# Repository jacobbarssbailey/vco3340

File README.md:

# VCO3340
This project provides tested plans for a 6HP Eurorack-format CEM3340 [CoolAudio 3340] VCO synthesizer module.

### Inputs
- V/OCT: Exponential (1V per octave) pitch input
- Lin FM: Linear frequency modulation
- Sync: Hard sync oscillator to external signal; requires audio-rate signal at approx. ±5V.
- Width: Set duty cycle of pulse output from 0-100% with ±2.5V signal; normalled to 0V, i.e. square wave output

### Outputs
All oscillator outputs (Sine, Triangle, Sawtooth, and Pulse) range from ±5V. The pulse input width is controlled by the Width input, and by default is a 50% duty cycle, i.e. Square wave.

## BOM 

Qty | Value            | Device                  | Package             | Parts                                                |
--- | ---------------- | ----------------------- | ------------------- | ---------------------------------------------------- |
2   | 10KΩ             | Pot (Alpha 9mm)         | 6mm                 | COURSE, FINE                                         |
8   | 3.5mm Jacks      |                         | Thonkiconn          | LINFM, PULSE, SAW, SIN, SYNC, TRI, V/OCT, WIDTH      |
4   | M06              | 2.54mm header           | Pin                 | CTRL, KNOB, OUT, POWER                               |
4   | M06              | 2.54mm header           | Socket              | CTRL, KNOB, OUT, POWER                               |
1   | M08X2            | 2.54mm header           | Pin                 | EXPANSION                                            |
3   |                  | 2.54mm                  | Jumper              |                                                      |
1   | M05x2            | 2.54mm header           | Shrouded            | POWER                                                |
2   | 100Ω             | Resistor                | 0805                | R1, R22                                              |
1   | 390Ω             | Resistor                | 0805                | R36                                                  |
2   | 470Ω             | Resistor                | 0805                | R9, R19                                              |
1   | 1KΩ              | Resistor                | 0805                | R32                                                  |
2   | 2.2KΩ            | Resistor                | 0805                | R34, R40                                             |
2   | 3.6KΩ            | Resistor                | 0805                | R23, R25                                             |
1   | 5.6KΩ            | Resistor                | 0805                | R2, R21                                              |
8   | 10KΩ             | Resistor                | 0805                | R5, R10, R27, R35, R38, R39, R41, R42                |
1   | 24KΩ             | Resistor                | 0805                | R20                                                  |
1   | 47KΩ             | Resistor                | 0805                | R3                                                   |
2   | 80KΩ             | Resistor                | 0805                | R28, R29                                             |
5   | 100KΩ            | Resistor                | 0805                | R4, R15, R16, R24, R30                               |
4   | 200KΩ            | Resistor                | 0805                | R14, R18, R26, R31                                   |
1   | 150KΩ            | Resistor                | 0805                | R6                                                   |
3   | 1MΩ              | Resistor                | 0805                | R7, R11, R13                                         |
1   | 1.5MΩ            | Resistor                | 0805                | R8                                                   |
2   | 1.0nF            | Capacitor               | 0805                | C1, C2                                               |
1   | 1.25nF           | Capacitor (CG0)         | 0805                | C6                                                   |
2   | 10nF             | Capacitor               | 0805                | C4, C5                                               |
11  | 100nF            | Capacitor               | 0805                | C3, C10, C11, C12, C13, C14, C15, C18, C19, C21, C22 |
2   | 1µF              | Capacitor               | 0805                | C8, C9                                               |
4   | 47µF             | Capacitor (Pol)         | PANASONIC_C         | C16, C17, C20, C23                                   |
1   | 10KΩ             | Trimpot                 | 2.54mm Multiturn    | SCALE                                                |
1   | 20KΩ             | Trimpot                 | 2.54mm Multiturn    | HIGHFREQ                                             |
1   | 50KΩ             | Trimpot                 | 2.54mm Multiturn    | SYMMETRY                                             |
1   | 100KΩ            | Trimpot                 | 2.54mm Multiturn    | DRIVE                                                |
2   |                  | DIODE                   | SOD-123             | D4, D5                                               |
3   |                  | DIODE                   | SOD-323             | D1, D2, D3                                           |
2   | 3904             | Transistor (NPN)        | SOT23               | Q1, Q2                                               |
1   |                  | LM79L05A                | SOT89               | U1                                                   |
1   |                  | MC78L05A                | SOT89               | U2                                                   |
1   | TL071            | OPAMP-SINGLE            | SO08                | IC1                                                  |
1   |                  | V3340/CEM3340           | SO16                | IC2                                                  |
1   |                  | LM397                   | SOT23-5             | IC3                                                  |
2   | TL072            | OPAMP-DUAL              | SO08                | IC4, IC5                                             |

## Notes on assembly:
1. The rear expansion header is not optional; the V/Oct, Pulse Width, and Soft Sync inputs *must* be connected to ground for proper operation
1. Non-shrouded headers may be used for the Power connector, but this makes it easier to invert the cable polarity, with potentially unpleasant results.

## First time setup
The four trim potentiometers must be set up before use. The following procedure is recommended:
1. Confirm that the V/Oct, Pulse Width, and Soft Sync inputs on the expansion header are connected to the neighboring ground pin (with jumpers)
1. Turn HIGHFREQ all the way down. The middle pin should be shorted to ground.
1. Adjust SCALE until V/Oct input tracks at 1V per octave from 40-60Hz to ≅2Khz. This step is the most difficult, but its critical for tuning. If available, compare against a reference VCO with good tracking. Alternative methods include measuring the pulse output with a frequency counter, or measuring with an external tuner.
1. Adjust HIGHFREQ up until higher frequencies track equally well.
1. Measure the SINE output. Adjust DRIVE and SYMMETRY until the output sounds like a Sine Wave. Using an Oscilloscope may make this easiest, but its not critical and your ears are an equally good reference.

## Expansion header

While the module is an excellent standalone module, the rear expansion header may be used to add additional controls or further manipulate outputs.

It can provide power rails to a sister module, but the ±5V rails should be limited to <50mA.

The external V/Oct pin duplicates the front-panel input. The Width input sets the default pulse width. The Soft Sync input is ready to use as is, and expects ±5V audio rate signals as input.

All output waveforms are provided for additional waveshaping.

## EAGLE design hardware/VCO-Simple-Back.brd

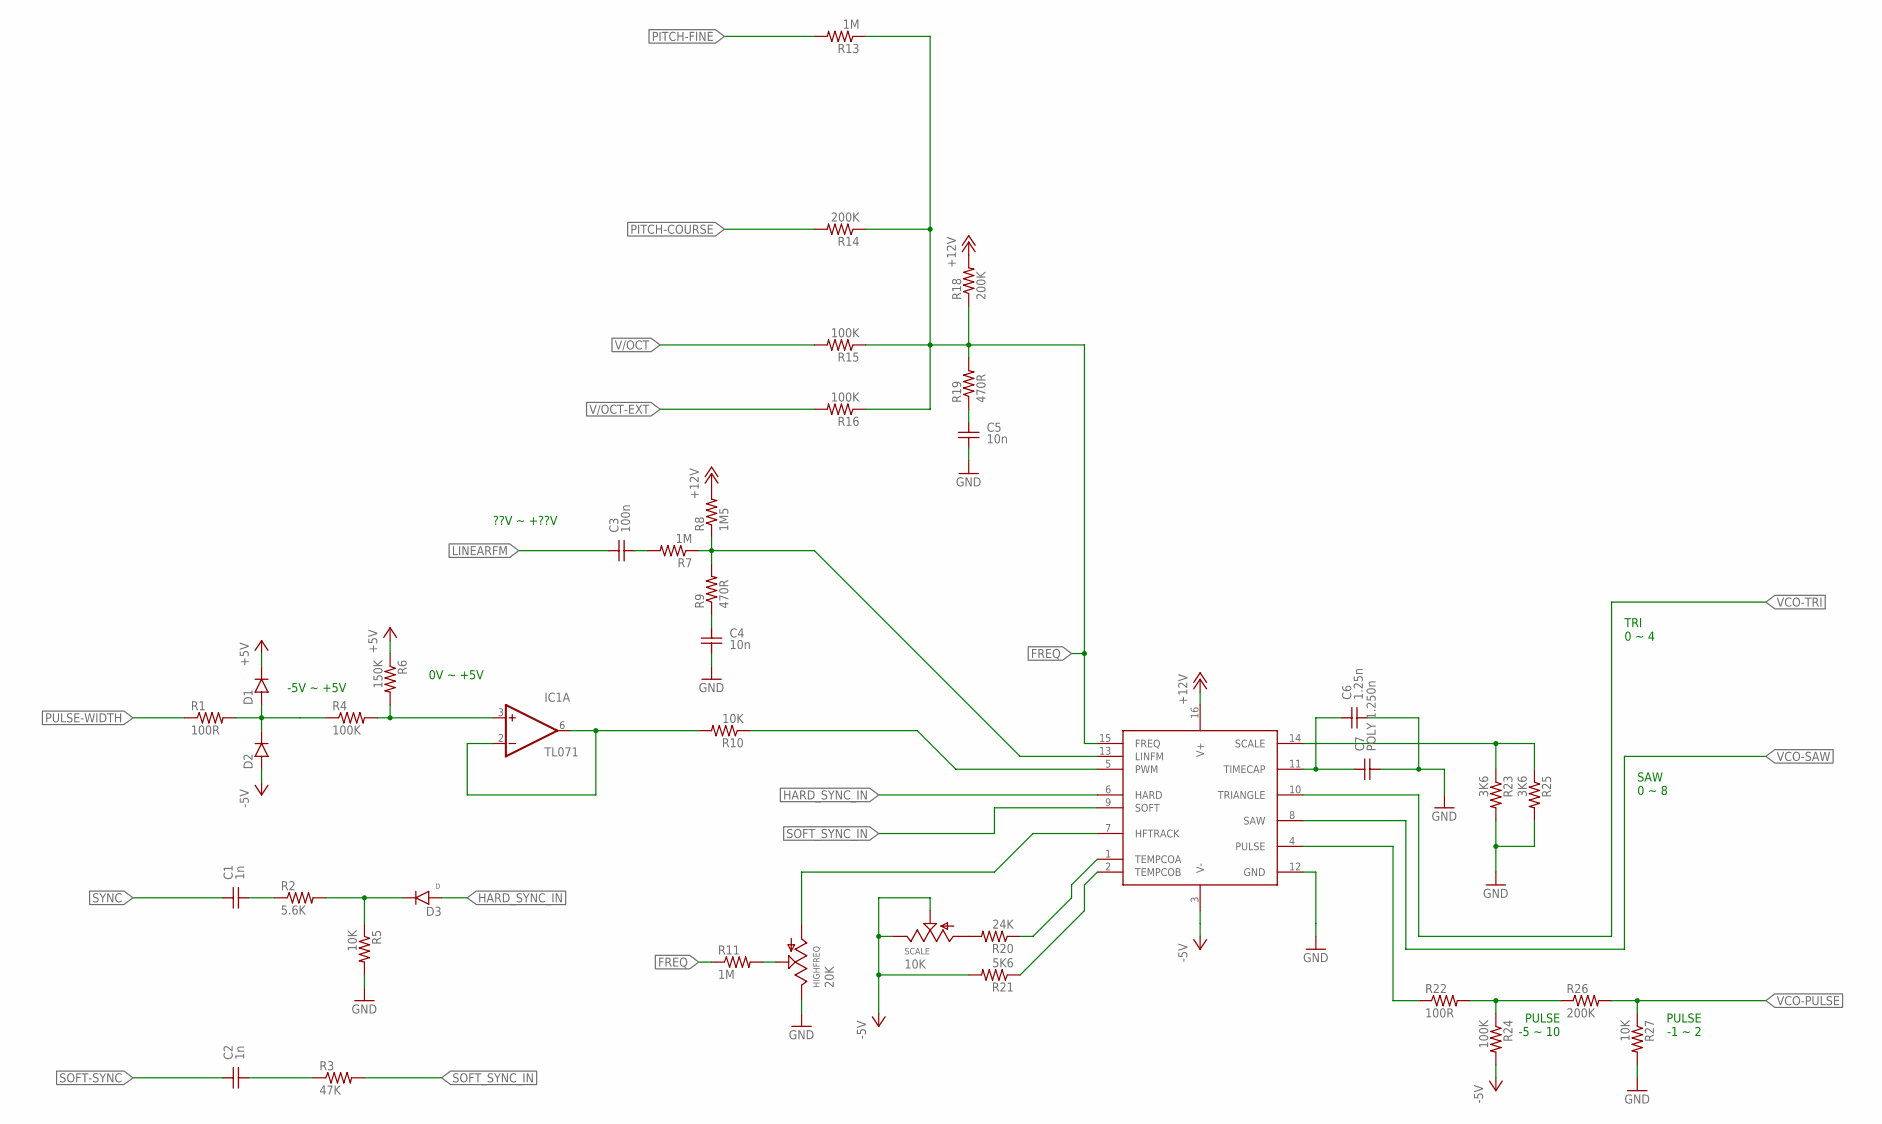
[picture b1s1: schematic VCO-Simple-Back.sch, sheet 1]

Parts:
C1, C2: 1n; C-0805
C3: 100n; C-0805
C4, C5: 10n; C-0805
C6: 1.25n; C-0805
C7: POLY 1.250n; CAP-5MM
D1, D2: DIODESOD-323; SOD-323
D3: D; SOD-323
HIGHFREQ: 20K; POT-TRIM-MULTI-V
IC1: TL071; SO08
IC2: V3340SO16; SO16
R1, R22: 100R; R-0805-MILL
R2: 5.6K; R-0805-MILL
R3: 47K; R-0805-MILL
R4, R15, R16, R24: 100K; R-0805-MILL
R5, R10, R27: 10K; R-0805-MILL
R6: 150K; R-0805-MILL
R7, R11, R13: 1M; R-0805-MILL
R8: 1M5; R-0805-MILL
R9, R19: 470R; R-0805-MILL
R14, R18, R26: 200K; R-0805-MILL
R20: 24K; R-0805-MILL
R21: 5K6; R-0805-MILL
R23, R25: 3K6; R-0805-MILL
SCALE: 10K; POT-TRIM-MULTI-V

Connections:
+5V: D1.K (C), R6.P$1 (1); also elsewhere on the board
+12V: IC2.16 (V+), R8.P$2 (2), R18.P$2 (2); also elsewhere on the board
-5V: D2.A, IC2.3 (V-), R21.P$2 (2), R24.P$2 (2), SCALE.B (E), SCALE.W (S); also elsewhere on the board
FREQ: IC2.15 (FREQ), R11.P$1 (1), R13.P$1 (1), R14.P$1 (1), R15.P$1 (1), R16.P$1 (1), R18.P$1 (1), R19.P$2 (2)
GND: C4.2, C5.2, C6.2, C7.2, HIGHFREQ.B (E), IC2.12 (GND), R5.P$2 (2), R23.P$2 (2), R25.P$2 (2), R27.P$2 (2); also elsewhere on the board
HARD_SYNC_IN: D3.A, IC2.6 (HARD)
LINEARFM: C3.1; also elsewhere on the board
unnamed: IC2.5 (PWM), R10.P$1 (1)
unnamed: C6.1, C7.1, IC2.11 (TIMECAP)
unnamed: HIGHFREQ.W (S), R11.P$2 (2)
unnamed: R20.P$2 (2), SCALE.A
unnamed: IC2.2 (TEMPCOB), R21.P$1 (1)
unnamed: D3.K (C), R2.P$2 (2), R5.P$1 (1)
unnamed: IC2.14 (SCALE), R23.P$1 (1), R25.P$1 (1)
unnamed: C5.1, R19.P$1 (1)
unnamed: C3.2, R7.P$2 (2)
unnamed: IC2.13 (LINFM), R7.P$1 (1), R8.P$1 (1), R9.P$2 (2)
unnamed: C4.1, R9.P$1 (1)
unnamed: HIGHFREQ.A, IC2.7 (HFTRACK)
unnamed: IC2.1 (TEMPCOA), R20.P$1 (1)
unnamed: D1.A, D2.K (C), R1.P$2 (2), R4.P$1 (1)
unnamed: R22.P$2 (2), R24.P$1 (1), R26.P$1 (1)
unnamed: C1.2, R2.P$1 (1)
unnamed: C2.2, R3.P$1 (1)
unnamed: IC1.3 (+IN), R4.P$2 (2), R6.P$2 (2)
PITCH-COURSE: R14.P$2 (2); also elsewhere on the board
PITCH-FINE: R13.P$2 (2); also elsewhere on the board
PULSE: IC2.4 (PULSE), R22.P$1 (1)
PULSE-WIDTH: R1.P$1 (1); also elsewhere on the board
PWMIN: IC1.2 (-IN), IC1.6 (OUT), R10.P$2 (2)
SOFT-SYNC: C2.1; also elsewhere on the board
SOFT_SYNC_IN: IC2.9 (SOFT), R3.P$2 (2)
SYNC: C1.1; also elsewhere on the board
V/OCT: R15.P$2 (2); also elsewhere on the board
V/OCT-EXT: R16.P$2 (2); also elsewhere on the board
VCO-PULSE: R26.P$2 (2), R27.P$1 (1); also elsewhere on the board
VCO-SAW: IC2.8 (SAW); also elsewhere on the board
VCO-TRI: IC2.10 (TRIANGLE); also elsewhere on the board

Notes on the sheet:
TRI 0 ~ 4
SAW 0 ~ 8
PULSE -5 ~ 10
PULSE -1 ~ 2
-5V ~ +5V
0V ~ +5V
??V ~ +??V

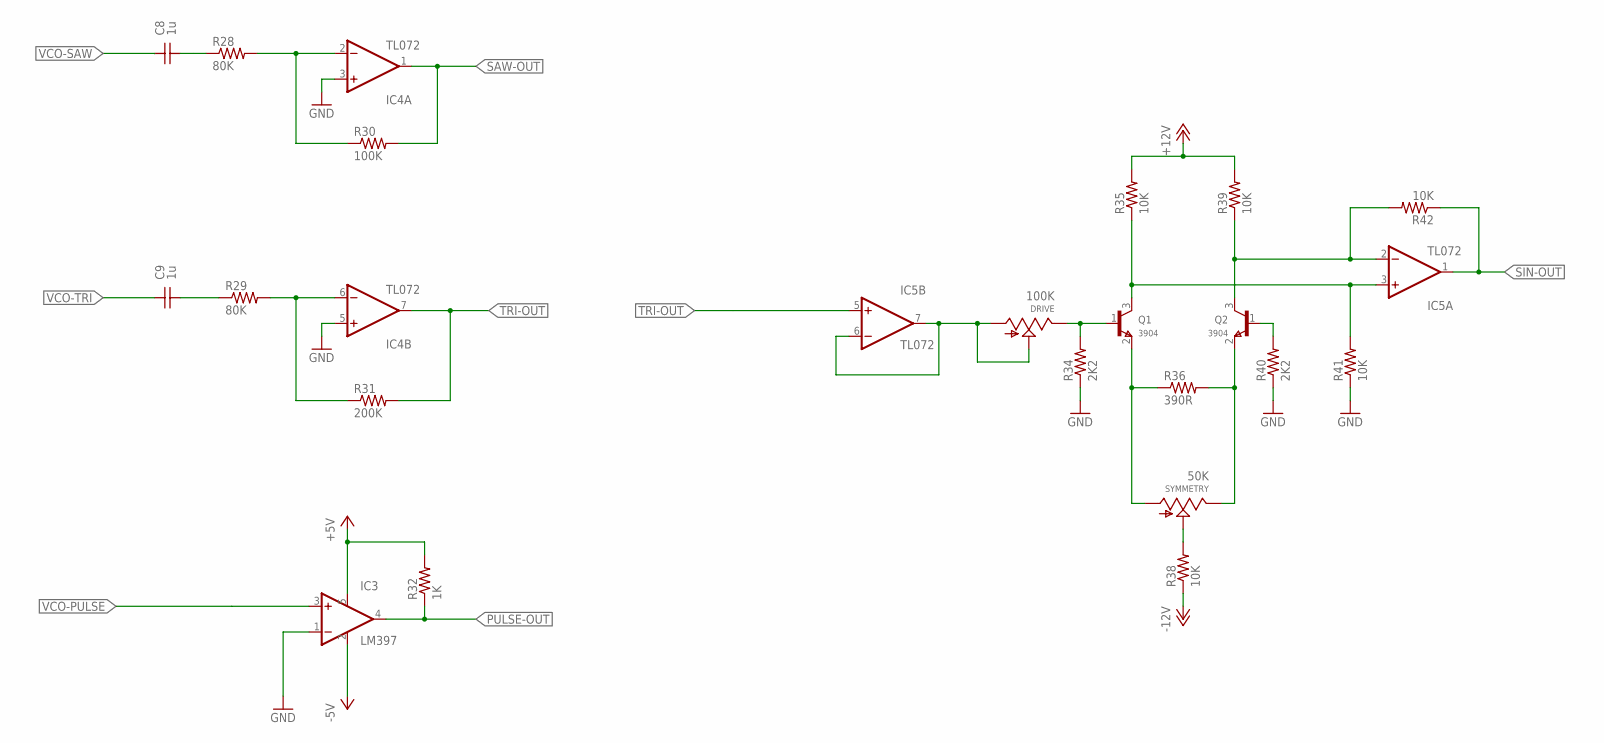
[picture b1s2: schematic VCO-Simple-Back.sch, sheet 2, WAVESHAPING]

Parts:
C8, C9: 1u; C-0805
DRIVE: 100K; POT-TRIM-MULTI-V
IC3: LM397; SOT23-5
IC4, IC5: TL072; SO08
Q1, Q2: 3904; SOT23
R28, R29: 80K; R-0805-MILL
R30: 100K; R-0805-MILL
R31: 200K; R-0805-MILL
R32: 1K; R-0805-MILL
R34, R40: 2K2; R-0805-MILL
R35, R38, R39, R41, R42: 10K; R-0805-MILL
R36: 390R; R-0805-MILL
SYMMETRY: 50K; POT-TRIM-MULTI-V

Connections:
+5V: IC3.5 (V+), R32.P$2 (2); also elsewhere on the board
+12V: R35.P$2 (2), R39.P$2 (2); also elsewhere on the board
-5V: IC3.2 (GND); also elsewhere on the board
-12V: R38.P$1 (1); also elsewhere on the board
GND: IC3.1 (-IN), IC4.3 (+IN), IC4.5 (+IN), R34.P$1 (1), R40.P$1 (1), R41.P$1 (1); also elsewhere on the board
unnamed: C8.2, R28.P$1 (1)
unnamed: C9.2, R29.P$1 (1)
unnamed: IC4.6 (-IN), R29.P$2 (2), R31.P$1 (1)
unnamed: IC4.2 (-IN), R28.P$2 (2), R30.P$1 (1)
unnamed: DRIVE.A, DRIVE.W (S), IC5.6 (-IN), IC5.7 (OUT)
unnamed: R38.P$2 (2), SYMMETRY.W (S)
unnamed: DRIVE.B (E), Q1.1 (B), R34.P$2 (2)
unnamed: Q1.2 (E), R36.P$1 (1), SYMMETRY.A
unnamed: Q2.2 (E), R36.P$2 (2), SYMMETRY.B (E)
unnamed: Q2.1 (B), R40.P$2 (2)
unnamed: IC5.2 (-IN), Q2.3 (C), R39.P$1 (1), R42.P$2 (2)
unnamed: IC5.3 (+IN), Q1.3 (C), R35.P$1 (1), R41.P$2 (2)
PULSE-OUT: IC3.4 (OUT), R32.P$1 (1); also elsewhere on the board
SAW-OUT: IC4.1 (OUT), R30.P$2 (2); also elsewhere on the board
SIN-OUT: IC5.1 (OUT), R42.P$1 (1); also elsewhere on the board
TRI-OUT: IC4.7 (OUT), IC5.5 (+IN), R31.P$2 (2); also elsewhere on the board
VCO-PULSE: IC3.3 (+IN); also elsewhere on the board
VCO-SAW: C8.1; also elsewhere on the board
VCO-TRI: C9.1; also elsewhere on the board

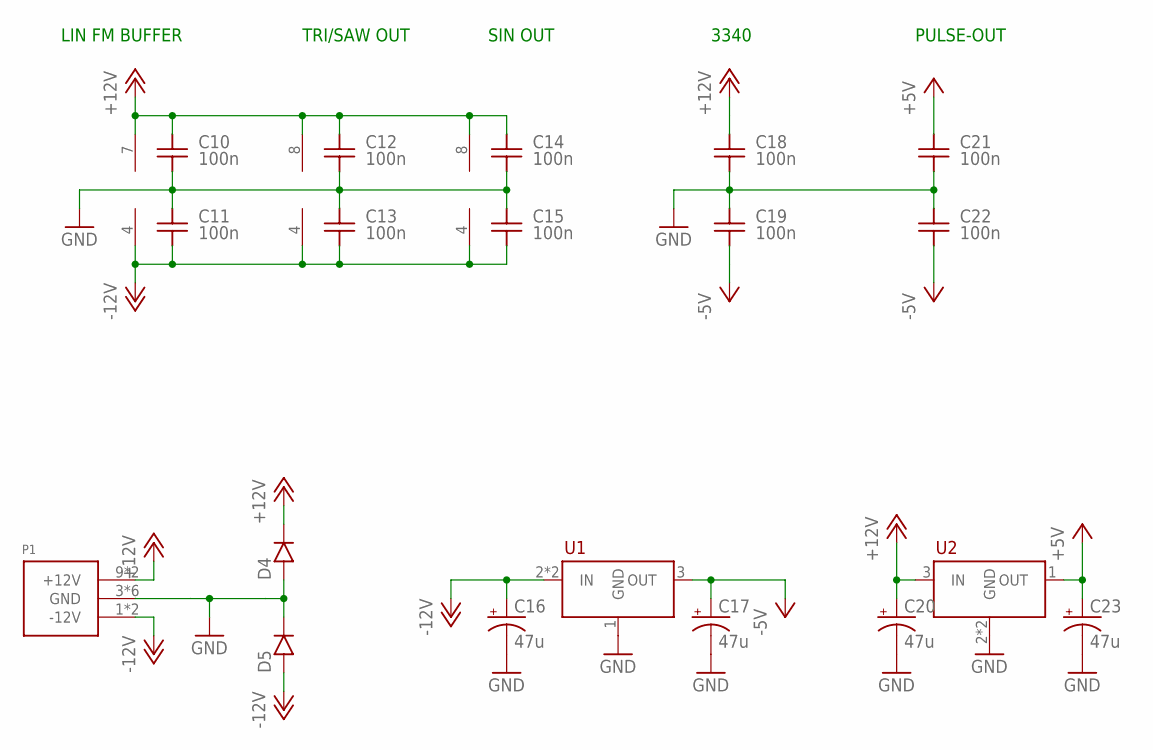
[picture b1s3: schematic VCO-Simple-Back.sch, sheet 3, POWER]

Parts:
C10, C11, C12, C13, C14, C15, C18, C19, C21, C22: 100n; C-0805
C16, C17, C20, C23: 47u; PANASONIC_C
D4, D5: DIODESOD-123; SOD-123
IC1: TL071; SO08
IC4, IC5: TL072; SO08
P1: POWER_SIMPLE10_SHROUDED; POWER_10_SHROUDED
U1: LM79L05A; SOT89
U2: MC78L05A; SOT89

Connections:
+5V: C21.1, C23.+, U2.1 (OUT); also elsewhere on the board
+12V: C10.1, C12.1, C14.1, C18.1, C20.+, D4.K (C), IC1.7 (V+), IC4.8 (V+), IC5.8 (V+), P1.9 (+12V), P1.10 (+12V), U2.3 (IN); also elsewhere on the board
-5V: C17.+, C19.2, C22.2, U1.3 (OUT); also elsewhere on the board
-12V: C11.2, C13.2, C15.2, C16.+, D5.A, IC1.4 (V-), IC4.4 (V-), IC5.4 (V-), P1.1 (-12V), P1.2 (-12V), U1.2 (IN), U1.2B (IN); also elsewhere on the board
GND: C10.2, C11.1, C12.2, C13.1, C14.2, C15.1, C16.-, C17.-, C18.2, C19.1, C20.-, C21.2, C22.1, C23.-, D4.A, D5.K (C), P1.3 (GND), P1.4 (GND), P1.5 (GND), P1.6 (GND), P1.7 (GND), P1.8 (GND), U1.1 (GND), U2.2 (GND), U2.2B (GND); also elsewhere on the board

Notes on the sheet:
LIN FM BUFFER
3340
TRI/SAW OUT
PULSE-OUT
SIN OUT

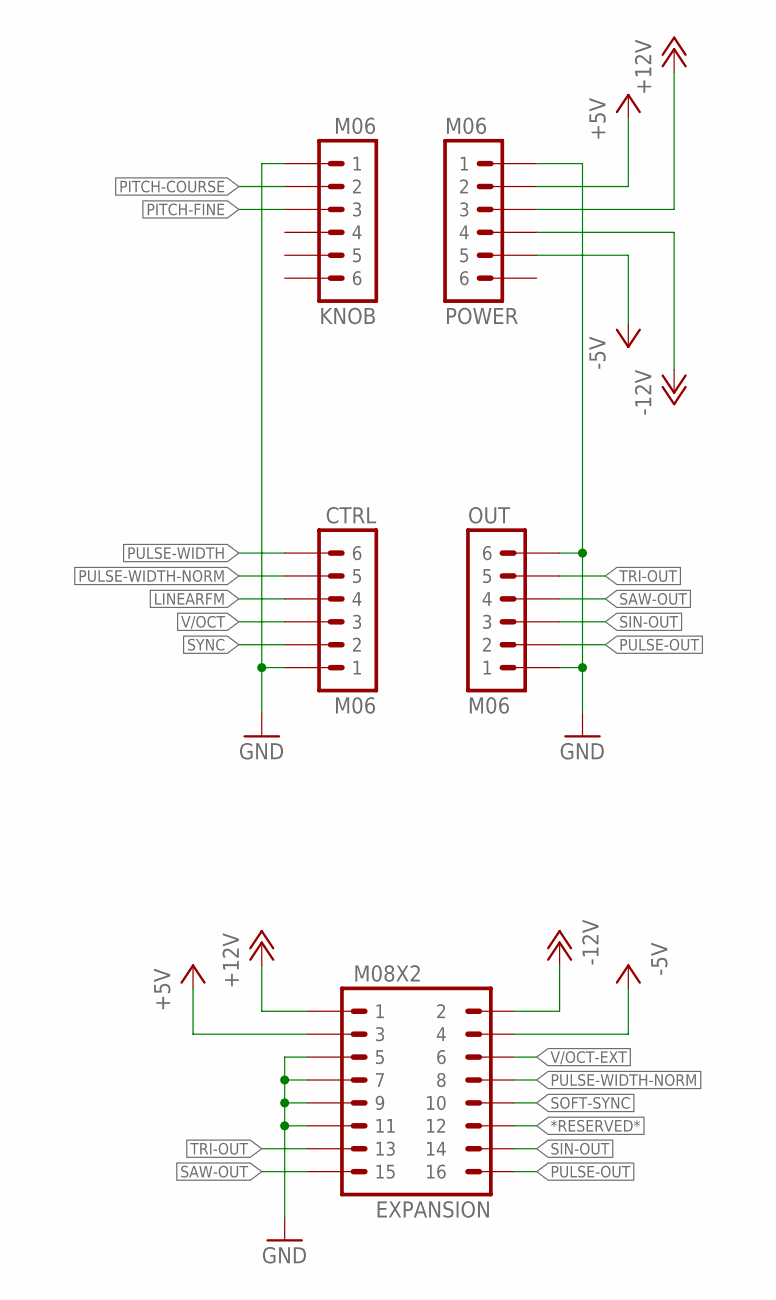
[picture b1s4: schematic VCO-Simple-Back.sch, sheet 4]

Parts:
CTRL: M06
EXPANSION: M08X2
KNOB: M06
OUT: M06
POWER: M06

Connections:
*RESERVED*: EXPANSION.12
+5V: EXPANSION.3, POWER.2; also elsewhere on the board
+12V: EXPANSION.1, POWER.3; also elsewhere on the board
-5V: EXPANSION.4, POWER.5; also elsewhere on the board
-12V: EXPANSION.2, POWER.4; also elsewhere on the board
GND: CTRL.1, EXPANSION.5, EXPANSION.7, EXPANSION.9, EXPANSION.11, KNOB.1, OUT.1, OUT.6, POWER.1; also elsewhere on the board
LINEARFM: CTRL.4; also elsewhere on the board
PITCH-COURSE: KNOB.2; also elsewhere on the board
PITCH-FINE: KNOB.3; also elsewhere on the board
PULSE-OUT: EXPANSION.16, OUT.2; also elsewhere on the board
PULSE-WIDTH: CTRL.6; also elsewhere on the board
PULSE-WIDTH-NORM: CTRL.5, EXPANSION.8
SAW-OUT: EXPANSION.15, OUT.4; also elsewhere on the board
SIN-OUT: EXPANSION.14, OUT.3; also elsewhere on the board
SOFT-SYNC: EXPANSION.10; also elsewhere on the board
SYNC: CTRL.2; also elsewhere on the board
TRI-OUT: EXPANSION.13, OUT.5; also elsewhere on the board
V/OCT: CTRL.3; also elsewhere on the board
V/OCT-EXT: EXPANSION.6; also elsewhere on the board

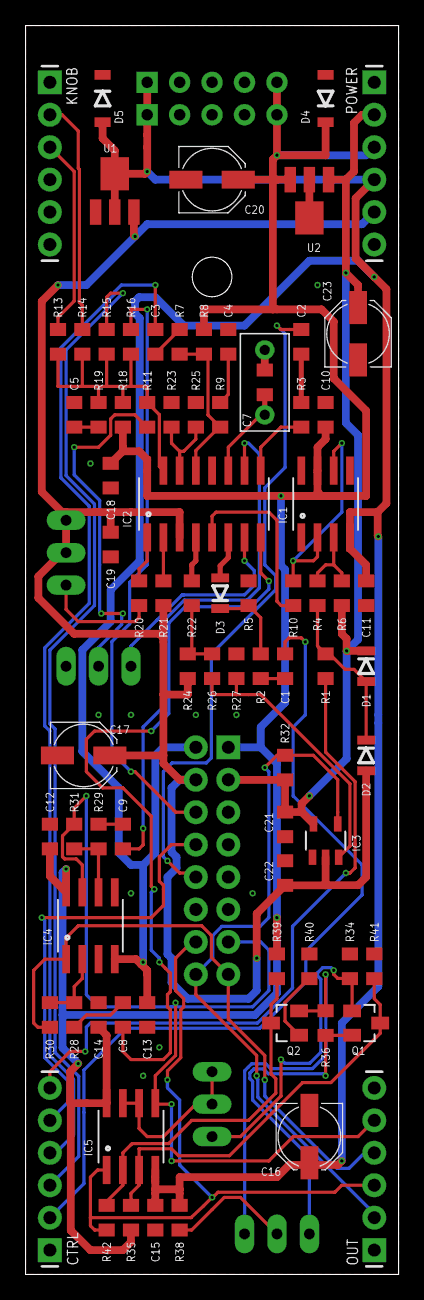
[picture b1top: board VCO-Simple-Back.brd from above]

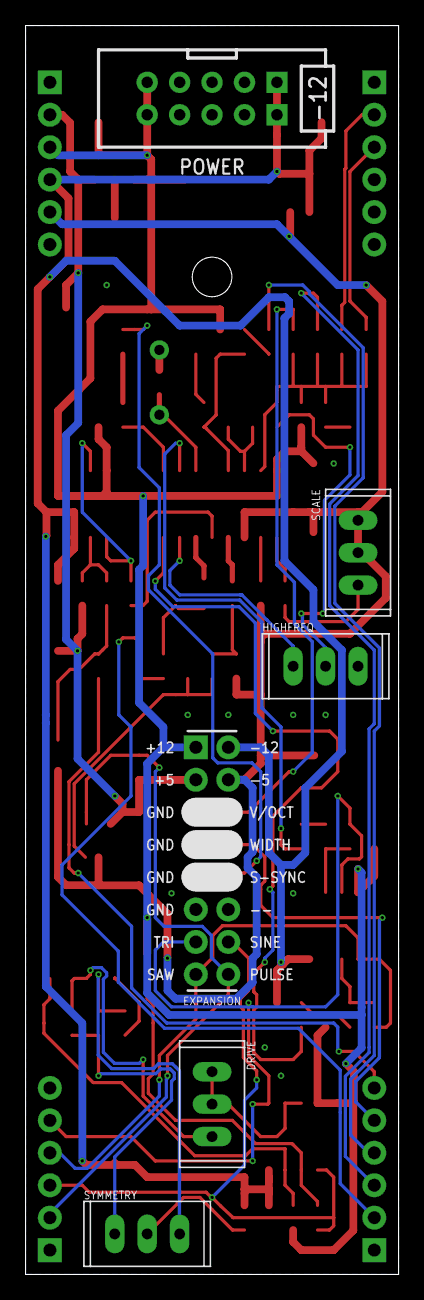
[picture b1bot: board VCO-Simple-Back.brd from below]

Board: 2 copper layers, 29.2 x 97.8 mm, 85 parts (6 on the bottom side), 56 nets.

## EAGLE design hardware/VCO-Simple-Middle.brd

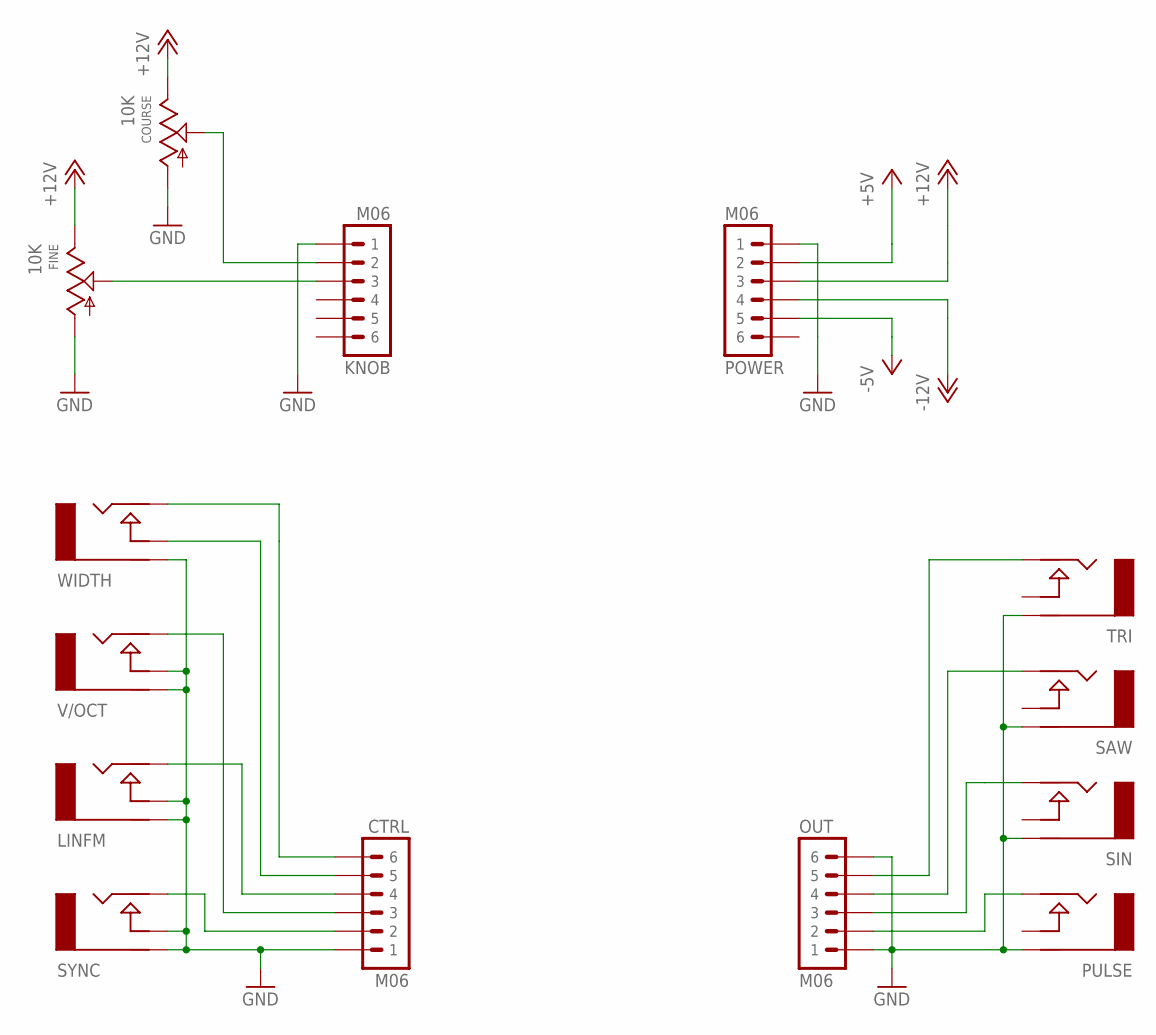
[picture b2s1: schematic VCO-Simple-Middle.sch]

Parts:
COURSE: 10K; POT-ALPHA-9MM
CTRL: M06
FINE: 10K; POT-ALPHA-9MM
KNOB: M06
LINFM: AUDIO-JACKINLINE; ERTHENVAR-JACK-INLINE
OUT: M06
POWER: M06
PULSE: AUDIO-JACKINLINE; ERTHENVAR-JACK-INLINE
SAW: AUDIO-JACKINLINE; ERTHENVAR-JACK-INLINE
SIN: AUDIO-JACKINLINE; ERTHENVAR-JACK-INLINE
SYNC: AUDIO-JACKINLINE; ERTHENVAR-JACK-INLINE
TRI: AUDIO-JACKINLINE; ERTHENVAR-JACK-INLINE
V/OCT: AUDIO-JACKINLINE; ERTHENVAR-JACK-INLINE
WIDTH: AUDIO-JACKINLINE; ERTHENVAR-JACK-INLINE

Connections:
+5V: POWER.2
+12V: COURSE.B (E), FINE.B (E), POWER.3
-5V: POWER.5
-12V: POWER.4
COURSE: COURSE.W (S), KNOB.2
FINE: FINE.W (S), KNOB.3
GND: COURSE.A, CTRL.1, FINE.A, KNOB.1, LINFM.G (RING), LINFM.N (NORM), OUT.1, OUT.6, POWER.1, PULSE.G (RING), SAW.G (RING), SIN.G (RING), SYNC.G (RING), SYNC.N (NORM), TRI.G (RING), V/OCT.G (RING), V/OCT.N (NORM), WIDTH.G (RING)
LIN: CTRL.4, LINFM.T (TIP)
PULSE: OUT.2, PULSE.T (TIP)
SAW: OUT.4, SAW.T (TIP)
SIN: OUT.3, SIN.T (TIP)
SYNC: CTRL.2, SYNC.T (TIP)
TRI: OUT.5, TRI.T (TIP)
V/OCT: CTRL.3, V/OCT.T (TIP)
WIDTH: CTRL.6, WIDTH.T (TIP)
WIDTH-NORM: CTRL.5, WIDTH.N (NORM)

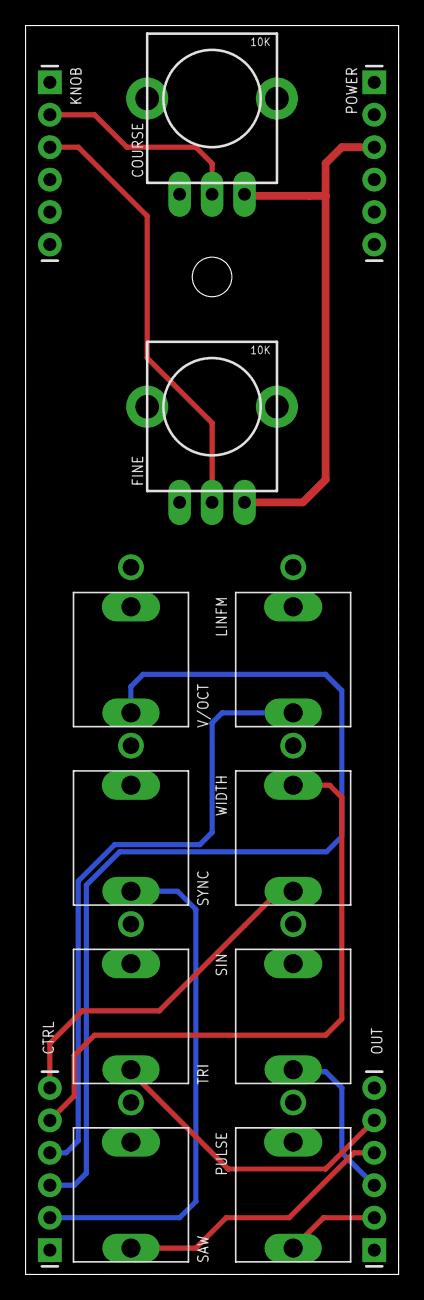
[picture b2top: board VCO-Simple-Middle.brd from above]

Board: 2 copper layers, 29.2 x 97.8 mm, 14 parts (0 on the bottom side), 13 nets.

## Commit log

2018-08-23 init
2018-09-14 revised component values
2018-09-14 updated readme with description, bom, assembly instructions
2018-09-14 add image, fix bom table dividers
2018-09-14 remove extra table divider
2018-09-14 spelling
2018-09-19 add page frames
2018-09-19 schematic pdfs
2018-09-20 typo
